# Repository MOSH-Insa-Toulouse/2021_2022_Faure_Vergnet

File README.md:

# LoRa Gas Sensor - ISS 2021-2022

**Paul Faure (IR), Arnaud Vergnet (IR)**

This repo contains the source files and some documentation on our mini project about creating a LoRa gas sensor based on nano-particles.

## Table of Contents

- [Content of this repository](#content-of-this-repository)
- [Mini Project](#mini-project)
  - [How the project works](#how-the-project-works)
  - [Node-Red Dashboard](#node-red-dashboard)

## Content of this repository

This repository contains several folders for each type of work.

- [arduino](arduino/): The Arduino source code used in the mini project
- [datasheet](datasheet/): The Datasheet made after the AIME lab on our gas sensor
- [img](img/): Images used in this README
- [kicad](kicad/): KiCad files for this mini-project and the Innovative project. We did not have time to create a fully working KiCad project for this mini project, but worked instead on the innovative project.
- [ltspice](ltspice/): LTspice project describing our Gas Sensor
- [node-red](node-red/): Node-Red flow exported in JSON format for the LoRa mini-project

## Mini Project

The source code used for this project is available in the [arduino](arduino/) folder.

We followed every track, from green to black. We will not go into details on how we solved each track, but will present on overview of our final solution.

### How the project works

We made the arduino source code modular by adding variables at the top to control which modules to enable.

Our mini-project is able to retrieve gas sensor values. It sends periodically those values using The Things Network (TTN). If a value goes over a cerain threshold, an alarm is triggered (buzzer). The state of the alarm is also sent over TTN. To reduce power consumption, it uses hardware interupts to wake up at specific intervals and read new values.

There a four LEDs indicating different states:
- The red LED will turn on when gas is detected, while the buzzer is buzzing
- The blue LED turns on when the arduino is connected to TTN
- The green LED turns on when the device is reading sensor data
- THe yellow LED turns on when the device is setup, indicating it is ready to read sensor data

Sadly, we did not take any picture of the finished product.

### Node-Red Dashboard

You will find bellow a screenshot of our node-red flow. This flow can be imported into node-red using the exported [JSON file](node-red/flows.json). It uses MQTT to connect to The Things Network, retrieves the payload from the json message and retrieves the alert and gas level values. It then shows the gas level value on a dashboard using a chart, and the alert status using a switch.

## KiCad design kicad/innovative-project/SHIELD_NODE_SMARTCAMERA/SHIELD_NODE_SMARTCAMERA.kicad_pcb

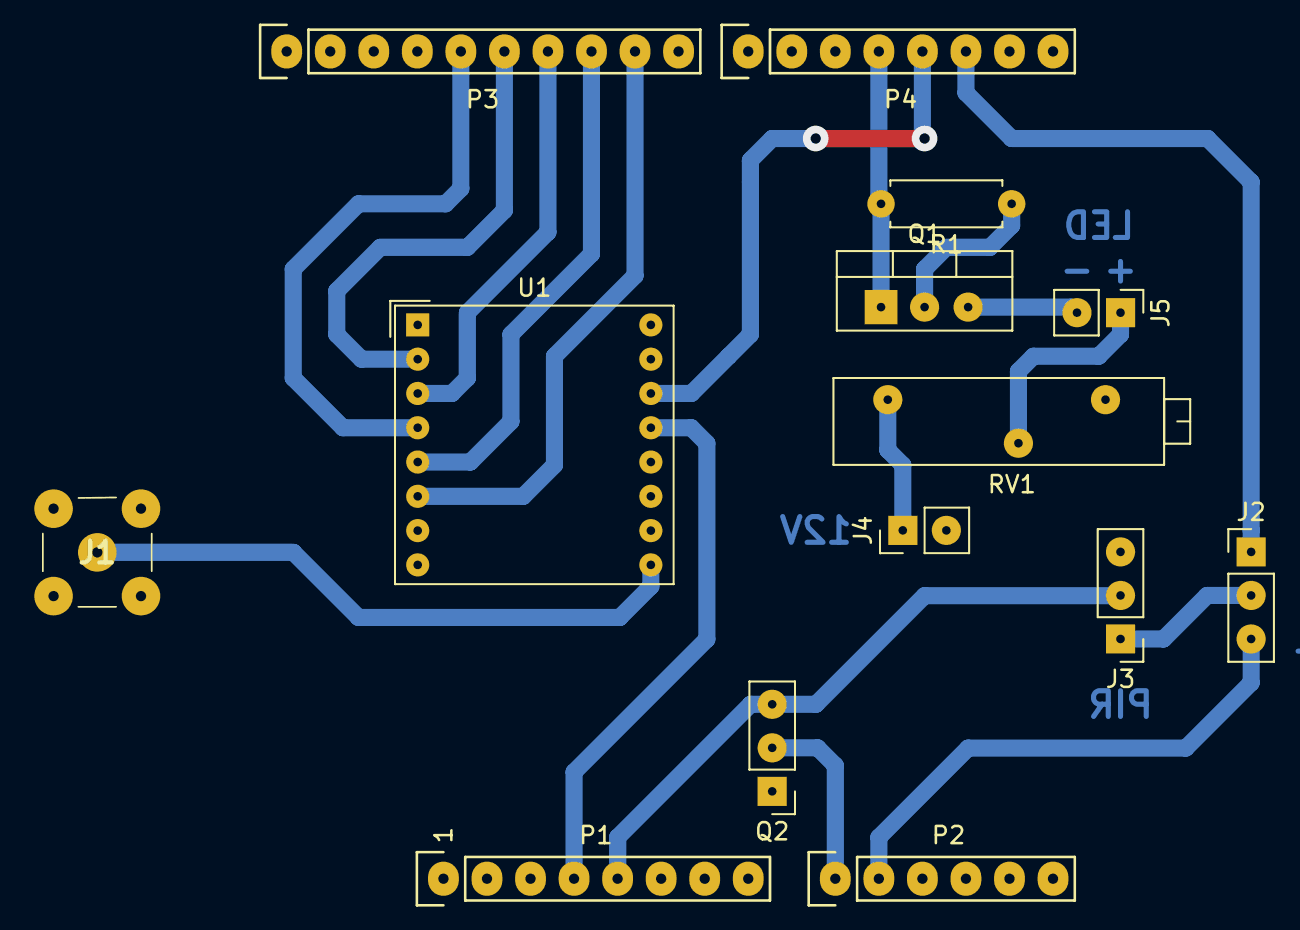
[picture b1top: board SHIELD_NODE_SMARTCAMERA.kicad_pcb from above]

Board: 2 copper layers, 14 parts (0 on the bottom side), 20 nets.

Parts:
J1: 1-1478979-0; 114789790
J2, J3: Conn_01x03; PinHeader_1x03_P2.54mm_Vertical
J4, J5: Conn_01x02; PinHeader_1x02_P2.54mm_Vertical
P1: Power; Socket_Strip_Arduino_1x08
P2: Analog; Socket_Strip_Arduino_1x06
P3: Digital; Socket_Strip_Arduino_1x10
P4: Digital; Socket_Strip_Arduino_1x08
Q1: IRFZ44N; TO-220-3_Vertical
Q2: TMP36; PinHeader_1x03_P2.54mm_Vertical
R1: 10k; R_Axial_DIN0207_L6.3mm_D2.5mm_P7.62mm_Horizontal
RV1: R_Potentiometer; Potentiometer_Bourns_3006P_Horizontal
U1: RFM95W-868S2; HOPERF_RFM9XW_THT

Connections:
+3V3: P1.4, U1.13 (3.3V)
+5V: J3.2, P1.5, Q2.3 (B)
+12V: J4.1, RV1.1
/2: J2.1, P4.6
/3(**): P4.5, U1.14 (DIO0)
/4: P4.4, Q1.1 (G), R1.2
/9(**): P3.9, U1.6 (RESET)
/10(**/SS): P3.8, U1.5 (NSS)
/11(**/MOSI): P3.7, U1.3 (MOSI)
/12(MISO): P3.6, U1.2 (MISO)
/13(SCK): P3.5, U1.4 (SCK)
/A0: P2.1, Q2.2 (C)
/A1: J2.3, P2.2
/A4(SDA): P2.5, P3.2
/A5(SCL): P2.6, P3.1
/LED_MOINS: J5.2, Q1.3 (S)
/LED_PLUS: J5.1, RV1.2
GND: J1.1, J1.2, J1.3, J1.4, J3.3, J4.2, P1.6, P1.7, P3.4, Q1.2 (D), Q2.1 (E), R1.1, U1.10 (GND)
unnamed: J1.5, U1.9 (ANT)
unnamed: J2.2, J3.1

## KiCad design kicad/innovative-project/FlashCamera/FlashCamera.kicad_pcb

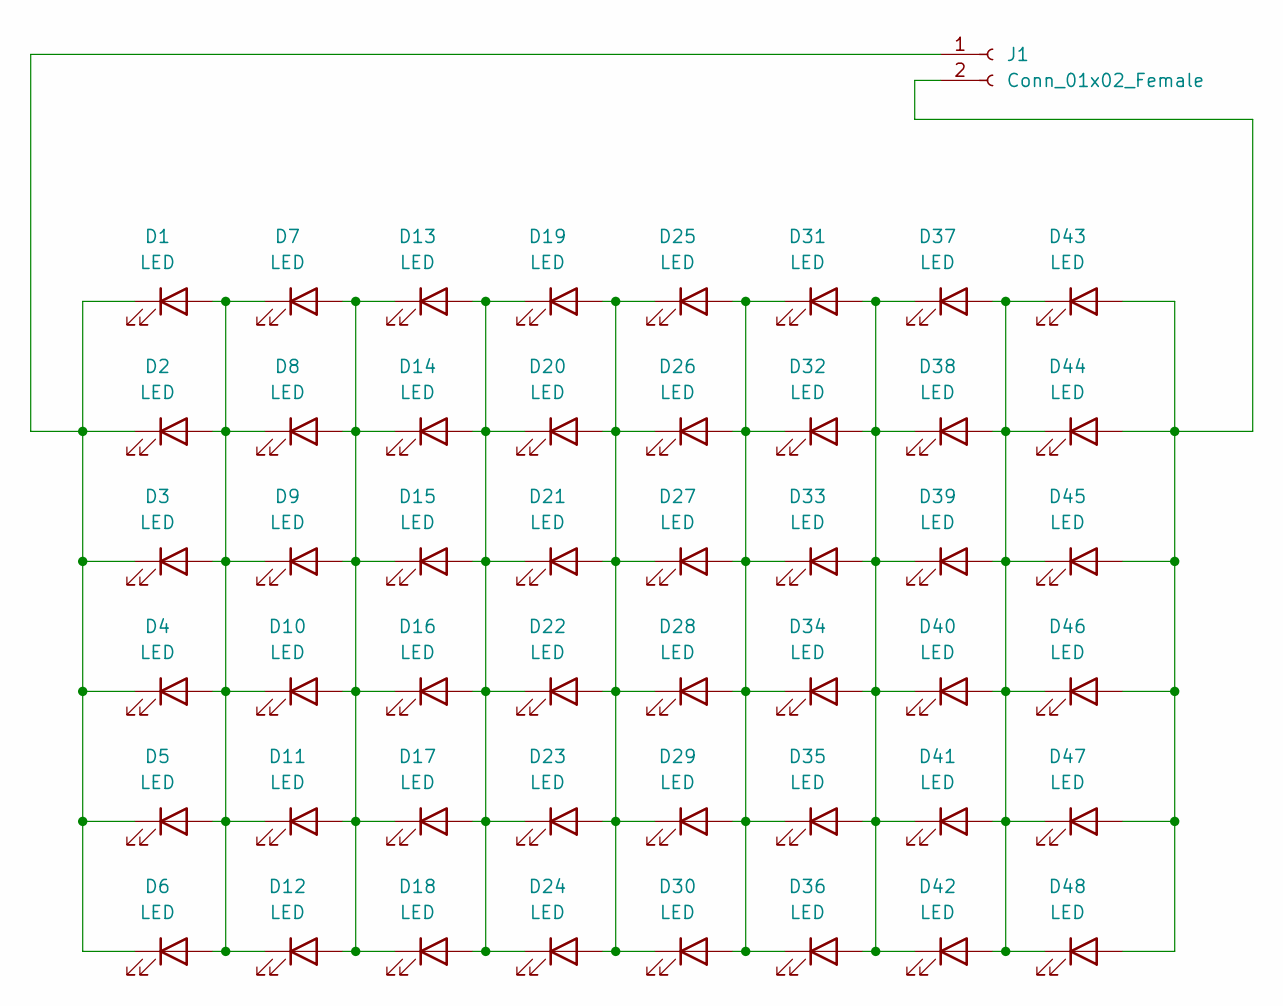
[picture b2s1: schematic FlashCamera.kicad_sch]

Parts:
D1, D2, D3, D4, D5, D6, D7, D8, D9, D10, D11, D12, D13, D14, D15, D16, D17, D18, D19, D20, D21, D22, D23, D24, D25, D26, D27, D28, D29, D30, D31, D32, D33, D34, D35, D36, D37, D38, D39, D40, D41, D42, D43, D44, D45, D46, D47, D48: LED; LED_D5.0mm
J1: Conn_01x02_Female; PinHeader_1x02_P2.54mm_Vertical

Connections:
unnamed: D1.1 (K), D2.1 (K), D3.1 (K), D4.1 (K), D5.1 (K), D6.1 (K), J1.1
unnamed: D1.2 (A), D2.2 (A), D3.2 (A), D4.2 (A), D5.2 (A), D6.2 (A), D7.1 (K), D8.1 (K), D9.1 (K), D10.1 (K), D11.1 (K), D12.1 (K)
unnamed: D7.2 (A), D8.2 (A), D9.2 (A), D10.2 (A), D11.2 (A), D12.2 (A), D13.1 (K), D14.1 (K), D15.1 (K), D16.1 (K), D17.1 (K), D18.1 (K)
unnamed: D13.2 (A), D14.2 (A), D15.2 (A), D16.2 (A), D17.2 (A), D18.2 (A), D19.1 (K), D20.1 (K), D21.1 (K), D22.1 (K), D23.1 (K), D24.1 (K)
unnamed: D19.2 (A), D20.2 (A), D21.2 (A), D22.2 (A), D23.2 (A), D24.2 (A), D25.1 (K), D26.1 (K), D27.1 (K), D28.1 (K), D29.1 (K), D30.1 (K)
unnamed: D25.2 (A), D26.2 (A), D27.2 (A), D28.2 (A), D29.2 (A), D30.2 (A), D31.1 (K), D32.1 (K), D33.1 (K), D34.1 (K), D35.1 (K), D36.1 (K)
unnamed: D31.2 (A), D32.2 (A), D33.2 (A), D34.2 (A), D35.2 (A), D36.2 (A), D37.1 (K), D38.1 (K), D39.1 (K), D40.1 (K), D41.1 (K), D42.1 (K)
unnamed: D37.2 (A), D38.2 (A), D39.2 (A), D40.2 (A), D41.2 (A), D42.2 (A), D43.1 (K), D44.1 (K), D45.1 (K), D46.1 (K), D47.1 (K), D48.1 (K)
unnamed: D43.2 (A), D44.2 (A), D45.2 (A), D46.2 (A), D47.2 (A), D48.2 (A), J1.2

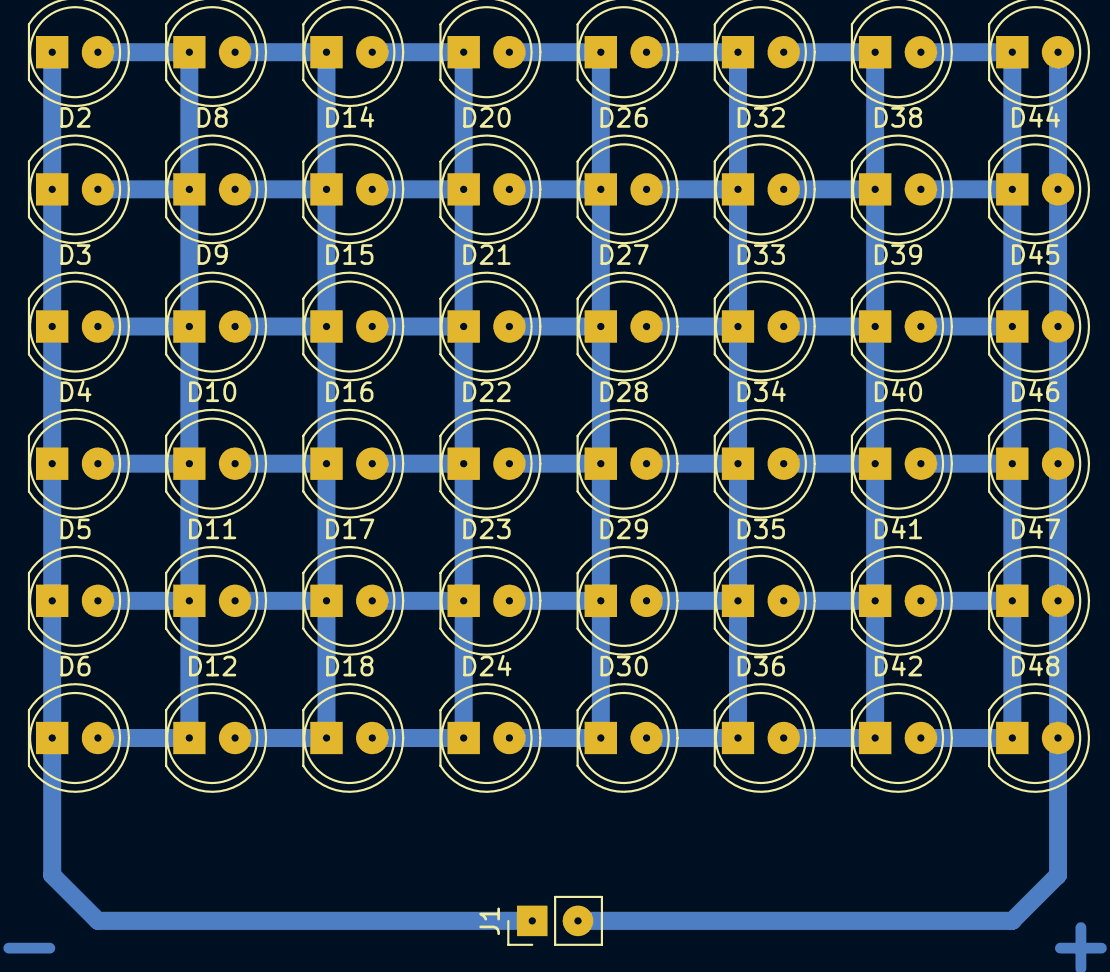
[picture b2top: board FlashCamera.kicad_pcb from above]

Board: 2 copper layers, 49 parts (0 on the bottom side), 9 nets.

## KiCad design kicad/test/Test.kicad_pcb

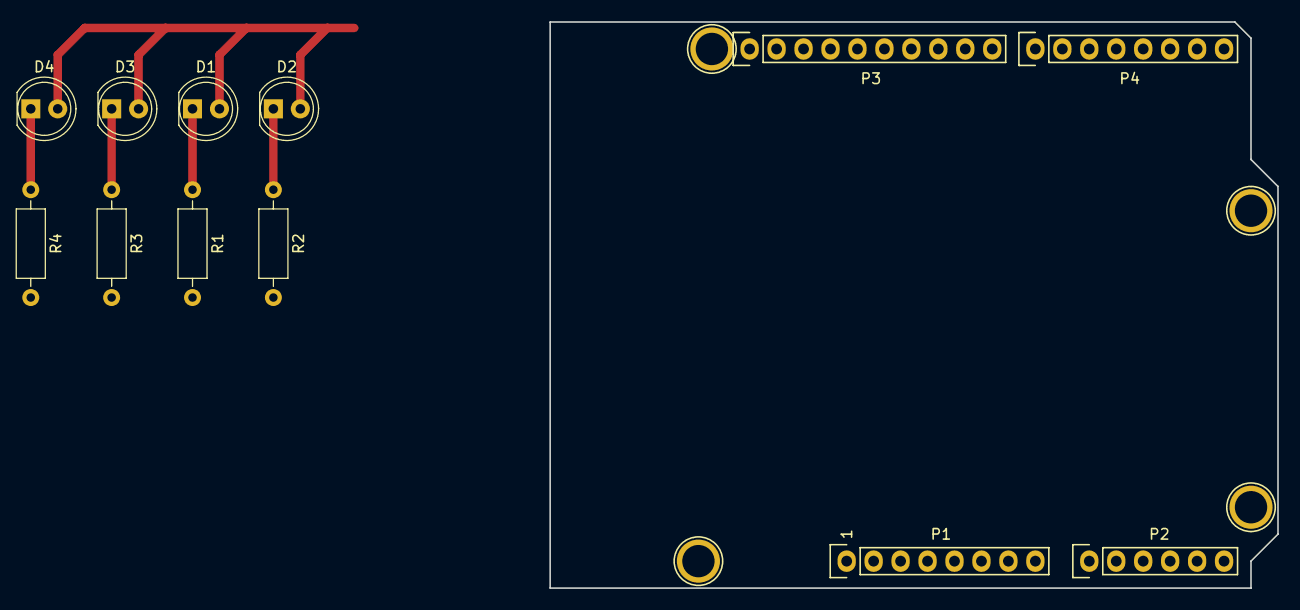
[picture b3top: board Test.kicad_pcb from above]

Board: 2 copper layers, 68.6 x 53.3 mm, 16 parts (0 on the bottom side), 11 nets.

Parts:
D1: LED_R; LED_D5.0mm
D2: LED_B; LED_D5.0mm
D3: LED_G; LED_D5.0mm
D4: LED_Y; LED_D5.0mm
P1: Power; Socket_Strip_Arduino_1x08
P2: Analog; Socket_Strip_Arduino_1x06
P3: Digital; Socket_Strip_Arduino_1x10
P4: Digital; Socket_Strip_Arduino_1x08
P5, P6, P7, P8: CONN_01X01; Arduino_1pin
R1, R2, R3, R4: 220; R_Axial_DIN0207_L6.3mm_D2.5mm_P10.16mm_Horizontal

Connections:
+5V: D1.2, D2.2, D3.2, D4.2, P1.5
/4: P4.4, R1.2
/5(**): P4.3, R2.2
/6(**): P4.2, R3.2
/A4(SDA): P2.5, P3.2
/A5(SCL): P2.6, P3.1
GND: P1.6, P1.7, P3.4, R4.2
unnamed: D1.1, R1.1
unnamed: D2.1, R2.1
unnamed: D3.1, R3.1
unnamed: D4.1, R4.1

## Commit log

2022-02-05 add arduino modes
